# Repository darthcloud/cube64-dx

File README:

======
cube64
======

Introduction
------------

This is a project to build an adaptor for using Gamecube controllers
with N64 consoles. The motivation behind this is that the N64 has some
really great games, but the controller hardware is rather bad- the
joysticks wear out quickly, and the layout is odd. The Gamecube
controllers, however, have a superset of the features and a much
better joystick.

A secondary goal of this project is to more thoroughly reverse engineer
the protocols involved and create reusable libraries for interfacing PIC
microcontrollers to N64 and Gamecube devices. The very basics of reverse
engineering the two protocols was done before I started this project,
but I quickly discovered that there's much more to the protocol. I believe
this project may be the first one to completely reverse engineer the
protocol used by standard N64 controllers, including peripherals like the
memory and rumble paks.

All code here is released under the GPL. This means that if you have basic
electronics skills and a way to program the microcontroller, you can build
your own cube64 adaptor easily. The hardware is extremely simple, and all
the complexity of reverse engineering and writing code is done for you ;)

Usage
-----

The completed adaptor plugs into an N64 console, and a regular Gamecube
controller or Wavebird (Only for 12f683 version) plugs into the adaptor. 
The default button mapping is as follows:

   Gamecube       N64
  ---------------------
   Analog stick   Analog stick
   D-pad          D-pad
   A              A
   B              B
   Z              Z
   Start          Start
   R end-stop     R
   L end-stop     L
   C-stick        C buttons
   X              C-down
   Y              B

This button mapping is stored in non-volatile memory, and may be modified during
gameplay. To change the mapping for one button:

  1. Hold down the L and R buttons down most of the way, but not enough to
     push the end-stop buttons, and press Start.

  2. If you have the rumble power connected, you should feel a brief rumble.

  3. Press the button you wish to remap. This includes the C-stick and D-pad, since
     they emulate buttons.

  4. Press the button you want to map it to. This button is always interpreted
     according to the above defaults, so for example pressing Y here would actually
     map to B. This has the effect that pressing the same button you pressed in step
     3 always resets that button to its default mapping.

  5. If the mapping was successful and you have rumble power connected, you should feel
     a brief rumble.

To reset all mappings of the current active button layout to the above defaults:

  1. Hold down the L and R buttons down most of the way, but not enough to
     push the end-stop buttons, and press Z.

  2. If you have the rumble power connected and the reset was successful, you should
     feel a brief rumble.

To toggle between displaying the controller with empty slot and occupied slot (See notes below):

  1. Hold down the L and R buttons down most of the way, but not enough to
     push the end-stop buttons, and press X.
	 
  2. If you have the rumble power connected and the toggle was successful, you should
     feel a brief rumble.

Note 1: 
	This setting is volatile. Adapter alway start as occupied on boot.

Note 2: 
	This feature is usefull for some game that repport error with a rumble pak.
	For those games, immediately toggle to empty controller on boot to avoid the error.

It is possible to save up to 4 sets of custom buttons layouts so you can easily use different keys
mapping in different games. To change between the preset do the following (Only available in 12F683 version):

  1. Hold down the L and R buttons down most of the way, but not enough to
     push the end-stop buttons, and press one of the direction on the gamecube "cross" pad.
	 
  2. If you have the rumble power connected and the preset change was successful, you should
     feel a brief rumble.
	 
  3. All preset by default hold the default button configuration. Just select one of 4
     presets and then change the button configuration using the button mapping key combo
	 described above.

  4. When you select a preset it is saved into the eeprom so the next time you power up
     the adaptor the last used preset will be load automaticaly!

The adaptor handles calibration in almost the exact same way a Gamecube does. If
your joystick is drifting or nonresponsive during gameplay, you should be able to
recalibrate it by performing any of the following actions without touching the
joystick, C-stick, L button, or R button:

  1. Hold down X, Y, and Start for a couple seconds during gameplay

  2. Unplug the controller from the adaptor and plug it back in

  3. Unplug the adaptor from the N64 and plug it back in

  4. Turn off the N64 then turn it back on. (The reset button won't
     recalibrate, since the adaptor doesn't lose power or get reinitialized)

Hardware
--------

There are currently three versions of the Cube64 hardware:

  - The "Cube64 Basic" uses a very common PIC16F84A microcontroller, and
    requires an external 5V power supply. Just about any electronics hobbyist
    should be able to build it easily. (Deprecated)

  - The "Cube64 Mini" uses a tiny 8-pin PIC12F629 microcontroller, and
    includes a charge pump that generates the 5V supply for the rumble motor.
    It is smaller and more convenient than the Cube64 Basic, but it requires
    a less common microcontroller and a charge pump that's only available
    in surface mount packages. (Deprecated)
	
  - The "Cube64-DX" uses the PIC12F683 microcontroller. It use exacly the same
    circuit as the Cube64 Mini. It's the only version who get new feature
	since it have more flash memory to hold the additional code needed.

Both older versions of the hardware have the same button remapping features
and responsiveness, as the only difference in their firmware is a few lines
worth of compile-time configuration. You can also of course use the charge
pump circuit from the Cube64 Mini with a PIC16F84A- but if you're using
tiny chips anyway, might as well go all the way ;)

The PIC12F683 version include all new feature like multi button mapping layout,
Wavebird support and a more accurate joystick value range.

Status
------

The protocol used between the N64 and controller, and between the controller
and controller pak is well-understood now. An RS-232 to N64 bridge and several
Python programs demonstrate just about all of the protocol.

The necessary subset of the protocol has been implemented in the cube64
firmware to emulate an official N64 controller with rumble pak. If 5V power
for the motor can be supplied to the gamecube controller, its rumble motor
will be used to emulate the N64 rumble pak.

It should be possible to emulate the N64 memory pak using the results of my
reverse engineering, but a 20 MHz PIC probably isn't fast enough to run the
CRC algorithm in time to return a status byte to the N64. If a faster
implementation of the CRC is discovered or a processor about twice as fast is
used, the memory pak could be emulated easily.

Contents
--------

  firmware:  Source code for the firmware, in PIC assembly. I develop this
             mostly using the open source "gputils" package, but I occasionally
             test it with MPLAB. The firmware for the adaptor itself is
             "cube64.asm", but there are a few additional test programs
             and libraries.

  hardware:  This includes schematics for the adaptor, in PDF and gschem format.

  notes:     Utilities and documentation produced while reverse engineering

Micah Dowty <micah@navi.cx>
Jacques Gagnon <darthcloud@gmail.com>

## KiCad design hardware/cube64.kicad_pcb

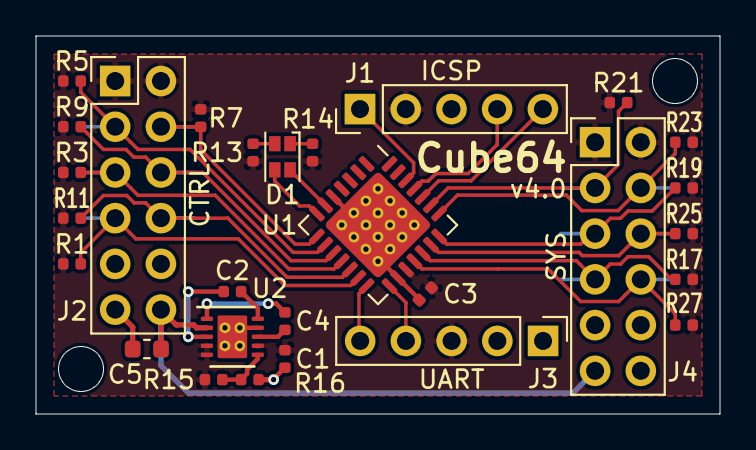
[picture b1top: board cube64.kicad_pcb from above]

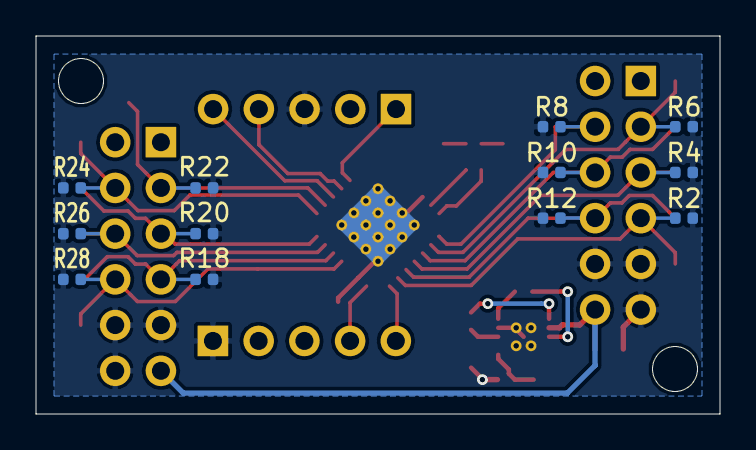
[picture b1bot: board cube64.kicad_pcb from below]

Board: 2 copper layers, 38.0 x 21.0 mm, 40 parts (12 on the bottom side), 29 nets.

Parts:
C1, C2, C4: 2.2u; C_0402_1005Metric
C3: 0.1u; C_0402_1005Metric
C5: 4.7u; C_0603_1608Metric
D1: LED_Dual_AACC; D_0606_1616Metric
J1: ICSP; PinHeader_1x05_P2.54mm_Vertical
J2: CTRL; PinHeader_2x06_P2.54mm_Vertical
J3: UART; PinHeader_1x05_P2.54mm_Vertical
J4: SYS; PinHeader_2x06_P2.54mm_Vertical
R1, R2, R4, R5, R6, R7, R8, R10, R11, R12, R17, R18, R19, R20, R21, R22, R23, R24, R25, R26, R27, R28: DNP; R_0402_1005Metric
R3, R9: 1K; R_0402_1005Metric
R13, R14: 64.9; R_0402_1005Metric
R15: 402K; R_0402_1005Metric
R16: 100K; R_0402_1005Metric
U1: PIC18F24Q10; QFN-28-1EP_6x6mm_P0.65mm_EP4.25x4.25mm_ThermalVias
U2: LTC3203B-1; DFN-10-1EP_3x3mm_P0.5mm_EP1.55x2.48mm

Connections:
+3V3: C1.1, C3.1, J1.2, J2.1, J2.2, J3.3, J4.1, J4.2, R1.1, R3.1, R5.1, R7.1, R9.1, R11.1, R13.1, R14.1, R15.1, R17.1, R19.1, R21.1, R23.1, R25.1, R27.1, U1.17, U2.4, U2.5, U2.7
+5V: C5.1, J2.12, J4.11, U2.2
/CTRL0: J2.4, R7.2, R8.1, U1.8
/CTRL1: J2.3, R5.2, R6.1, U1.9
/CTRL2: J2.6, R9.2, R10.1, U1.10
/CTRL3: J2.5, R3.2, R4.1, U1.11
/CTRL4: J2.8, R11.2, R12.1, U1.12
/CTRL5: J2.7, R1.2, R2.1, U1.13
/G_LED: D1.3, U1.6
/PGC: J1.5, U1.24
/PGD: J1.4, U1.25
/R_LED: D1.4, U1.7
/SYS0: J4.3, R21.2, R22.1, U1.23
/SYS1: J4.4, R23.2, R24.1, U1.22
/SYS2: J4.5, R19.2, R20.1, U1.21
/SYS3: J4.6, R25.2, R26.1, U1.20
/SYS4: J4.7, R17.2, R18.1, U1.19
/SYS5: J4.8, R27.2, R28.1, U1.18
/UART_RX: J3.4, U1.15
/UART_TX: J3.5, U1.14
GND: C1.2, C3.2, C5.2, J1.3, J2.9, J2.10, J2.11, J3.1, J4.9, J4.10, J4.12, R2.2, R4.2, R6.2, R8.2, R10.2, R12.2, R16.2, R18.2, R20.2, R22.2, R24.2, R26.2, R28.2, U1.5, U1.16, U1.29, U2.9, U2.11
unnamed: C2.1, U2.3
unnamed: C2.2, U2.10
unnamed: C4.1, U2.1
unnamed: C4.2, U2.8
unnamed: D1.1, R14.2
unnamed: D1.2, R13.2
unnamed: R15.2, R16.1, U2.6
VPP: J1.1, U1.26

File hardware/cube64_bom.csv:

Component,Description,Part,References,Value,Footprint,Quantity Per PCB,Datasheet,Digikey Part
1,Unpolarized capacitor,C,C3,0.1u,C_0402_1005Metric,1,~,1276-1004-1-ND
2,Unpolarized capacitor,C,C1 C2 C4,2.2u,C_0402_1005Metric,3,~,1276-1888-1-ND
3,Unpolarized capacitor,C,C5,4.7u,C_0603_1608Metric,1,~,1276-1907-1-ND
4,"LED dual, 4-pin",LED_Dual_AACC,D1,LTST-C195KGJRKT,D_0606_1616Metric,1,https://media.digikey.com/pdf/Data%20Sheets/Lite-On%20PDFs/L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,160-1452-1-ND
5,Resistor US symbol,R,R16,100K,R_0402_1005Metric,1,~,RMCF0402JT100KCT-ND
6,Resistor US symbol,R,R3 R9,1K,R_0402_1005Metric,2,~,311-1.0KJRCT-ND
7,Resistor US symbol,R,R15,402K,R_0402_1005Metric,1,~,YAG3151CT-ND
8,Resistor US symbol,R,R13 R14,64.9,R_0402_1005Metric,2,~,RMCF0402FT64R9CT-ND
9,,LTC3203B-1,U2,LTC3203B-1,DFN-10-1EP_3x3mm_P0.5mm_EP1.55x2.48mm,1,http://www.linear.com/docs/15197,LTC3203BEDD-1#PBF-ND
10,,PIC18F24Q10,U1,PIC18F24Q10,QFN-28-1EP_6x6mm_P0.65mm_EP4.25x4.25mm_ThermalVias,1,http://www.microchip.com/mymicrochip/filehandler.aspx?ddocna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,PIC18F24Q10-I/ML-ND





Component Groups:,13
Component Count:,40
Fitted Components:,14
Number of PCBs:,1
Total components:,14
Schematic Version:,A
Schematic Date:,2018-10-10
BoM Date:,Wed 10 Oct 2018 10:24:46 PM EDT
Schematic Source:,cube64-dx/hardware/cube64.sch
KiCad Version:,Eeschema 5.0.0-fee4fd1~66~ubuntu18.04.1

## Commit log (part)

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2004-08-06 Move cube64 into wasabi/devices, it seems to be the trendy place to be these days
2004-08-06 Sprinkle this with #ifdef'ed no-ops that might magically make this work at 24 MHz too
2004-08-07 Some N64/gamecube timing fixes for 24Mhz. This is still untested, but it works in my head...
2011-03-26 cube64.asm: -Added support for identify command 0xFF. (Fixed issue #2) -Added support for 12F683 micro.
    Makefile:
    -Added support for 12F683 micro.
    n64gc_comm.inc:
    -Added support for identify command 0xFF. (Fixed issue #2)
    -Fixed typo about n64/ngc serial format.
2011-03-28 cube64.asm: -Added possibility to toggle between controller status id. Either occupied or empty with AL+AR+X key combo. (Enhancement #4 done)
2011-03-29 cube64.asm: -Added support for Wavebird (Enhancement #5 done) -Skip rumble update when in mode "slot empty"
2011-03-29 cube64.asm: -Minor typo in CRC table address for smaller PIC.
2011-03-31 cube64.asm: -Removed very ugly code repetition in the multi key layout selection section.
2011-04-02 cube64.asm: -GameCube axis range ~[24, 232] now correctly translated into N64 axis range ~[-84, 84]. (Fixed issue #7)
2011-04-02 Created wiki page explaining how to compile from source.
2011-04-03 Created wiki page to show how to program the PIC
2011-04-03 Edited wiki page WikiProgrammingThePIC through web user interface.
2011-04-03 Typo fixing.
2011-04-03 Edited wiki page Readme through web user interface.
2011-04-04 cube64.asm: -Unlike what is write in many source for both N64 and Gamecube, the controller response always end with a 2us stop bit. In Micah docs he say this is only done for CRC response. But from w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
    So I removed the n64_tx_widestop and modified n64_tx to always used 2us stop bit.
2011-04-04 Deleting wiki page WikiCompilingFromSource.
2011-04-04 Deleting wiki page WikiProgrammingThePIC.
2011-04-13 cube64.asm: -Their where not any n64_status_buffer initialization when a Wavebird receiver is not associated with a WB. Added n64_status_buffer initialization at the beginning. (Fixed issue #8)
2011-04-13 cube64.asm: -Better fix of n64_status_buffer bug with Wavebird, always clear buffer before calling n64_wait_for_command. -When a Wavebird is connected to the adapter, Cube64-DX now report to the n64 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
2011-04-13 cube64.asm: -Little code cleanup.
2011-04-14 cube64.asm: -Now EEPROM reset combo only affect the current active button mapping layout.
2011-04-15 Added schematic for PIC12F683
2011-04-17 cube64.asm: -Fixed a bug with 16F84A EEPROM introduced by multi layout feature in 12F683 version.
2011-04-17 Edited wiki page BuildingAdapter through web user interface.
2011-04-17 Some change to reflect current adapter status.
2011-04-20 Removed support for older microcontroller.
    cube64.asm:
    -Added a deadzone to the GC joystick to fix some issue with Wavebird.
2011-04-22 cube64.asm: -Some little cleanup in variable declaration.
2011-04-28 Edited wiki page FlashingFirmware through web user interface.
2011-05-08 cube64.asm: -Implemented new key combo handling method. All option are accessed now via a config menu (Accessed by pressing AL+AR+Start). Once in the menu you can enter remap function by pressing Sta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
    Their is two submenu currently. The adapter mode submenu is accessed by pressing D-pad UP while the button layout submenu is accessed by pressing D-pad LEFT.
    In adapter mode submenu pressing UP make the adapter show as controller with empty slot while pressing LEFT make it show as controller with Rumble Pak.
    In layout selection submenu, each D-pad direction select one of the 4 button mapping layout.
2011-05-08 cube64.asm: -Now possible to select on boot the adapter mode by pressing the D-pad direction. Option layout is the same as the layout selection submenu.
2011-08-13 cube64.asm: -Redone some CR removed with last commit.
2011-11-03 Added new folder (firmware64) for upcoming implementation running at 64MHz.
2011-12-06 New firmware version running on PIC18F14K22 @ 64MHz.
2018-01-04 Make EEPROM mapping more versatile
    Will allow additional axes & buttons to be remapped.
2018-01-04 Add .gitignore
    Ignore hex, cod, lst & pyc files
2018-01-04 Use TMR0 for rumble feedback time base
    Using system polling rate could often result in rumble to be too short to be felt.
    This provides a consistent 250 ms rumble feedback.
2018-01-04 Get ride of the TABs
    This break blame but it's a good tradeoff IMHO :)
2018-01-04 Add second config byte in EEPROM for each virtual buttons
    Required for future features.
2018-01-04 Split out definitions in cube64.inc file
2018-01-04 Cleanup configuration menu implementation
    Cosmetic only, no behavior change.
2018-01-04 Turn modifier bit into special function bit
    Will be used for additional internal functions.
2018-01-04 Make virtual buttons definitions more future proof
    That should allow changing the front end to any modern controllers.
2018-01-04 Add realtime CRC computation base on the large table
    This fix Banjo-Kazooie & GoldenEye 007 Rumble Pak mode (Issue #1)
2018-01-04 Specify python2 in scripts header
2018-01-04 Update documentation for v3.0 release
2018-01-04 New firmware version running on PIC18F14K22 @ 64 MHz
    Port Cube64 from PIC12F683 @ 20 MHz to PIC18F14K22 @ 64 MHz.
    The speed increase will allow computing the CRC.
2018-01-04 Revert "Firmware64"
2018-01-04 Add function to modify mapping layout with a button press
    Pressing the Y button at the top level menu will allow
    mapping a special function to the source button.
    The destination consists of one of the 4 D-pad directions who
    correspond respectively to one of the mapping layouts.
    While holding a button set to this function, the current
    mapping layout configured will be overwritten until
2018-01-04 N64 bus read now receive the 2 address bytes
    If the address is 0x8001 we answer with a packet of 0x80s.
    Otherwise send 0x00s.
    This make us answer a bit slower (~14 μs) than before (~10 μs) but
    the N64 gonna wait for us up to 80 μs base on my tests.
2018-01-04 Default serial bridge to normal polarity and script to /dev/ttyUSB0
    For use with FTDI TL-232R-3V3 cable.
2018-01-04 Allow selecting either digital or analog triggers for mapping
    By default button remap and special function combos will map to
    digital trigger buttons only.
    Pressing X in the main menu before either Start or Y will enable
    mapping to the analog trigger axes.
2018-01-04 Script for polling N64/GC SI bus devices
    This script uses the serial bridge and pool in loops
    for the buttons status.
    It currently supports N64 controllers, N64 mouses & GameCube controllers.
2018-01-05 Clear FLAG_TRIGGER when special function map abort
    The trigger flag would remain set if an invalid option was
    chosen in the special function mapping.
2018-02-06 Update documentation for v3.1 release
2018-02-06 Port Python 2 scripts to Python 3
    Use pySerial for serial bridge communication.
    Convert string usage to bytes.
    Fix prints and sorts.
2018-02-06 Add bypass mode for using N64 controller as accessory slot
    Fixes #10
    The adaptor can now have a N64 controller attach to it on RA2 to be
    used as an accessory slot. Once in this mode the adaptor will only
    answer the button status commands. All other commands will be copied to
    the N64 controller. Then the controller response is copied back to the
    system.
2018-05-22 Make adaptor mode non-volatile
    Quick hack to save the last used mode in EEPROM.
    Not in the main branch as I don't really like it myself. :)
    But some might prefer this.
2018-06-01 Add access bits
2018-06-01 Update documentation for v3.2 release
2018-06-01 Switch to banked access
    Will need to use the access mode for literal offset addressing later.
2018-06-01 Split joystick scaling on/off switch on two buttons
    Easier to tell if it's on or off.
2018-06-01 Align in-line comments
2018-06-06 Support 1 player 2 controllers control style
    GoldenEye and Perfect Dark got a control style using
    two controllers as a way to get dual analog sticks.
    Since the adaptor is now interrupt base it's quite easy now
    to answer another poll on another pin.
    This duplicate the mapping of the C buttons (as analog) and R buttons into
    second set of buffers for the second controller.
2018-06-21 Move 2nd controller pin to PORTB6
    Let's not overlap with the UART RX pin.
2018-06-21 Update documentation for v3.3 release
2018-06-21 Add LED to indicate we are in the menu
2018-06-21 Answer N64 poll within WaveBird init
2018-06-21 Add response curves option for each GC joystick axes
    This feature adds a new menu option DPAD-RIGHT in the top menu. Once in
    that submenu you can select one of the four joysticks axes of the GC
    controller by pressing either direction of one of those axes. Finally at
    the last level of the submenu you can select the following options:
    D-PAD UP: Map selected joystick axis through an aggressive response curve.
    D-PAD LEFT: Map selected joystick axis through a relaxed response curve.
2018-06-21 Mute joysticks input while in menu
2018-07-07 Restore RA4 transition detection in serial bridge
    Somehow the published version from 2004 do not check for
    transition on RA4, it rather sent TMR0 value.
    Fix up as well couple Python 3 script issue.
    It's purely academic but it allows recreating Micah original
    experiment from 2004!
    Traces done with the serial bridge on the controller bus are
2018-10-06 Pre-defined mapping layout presets
    Add a new entry in the main menu via D-pad DOWN for pre-defined mapping layout presets.
    Eight preset are available on flash to be copied in one of the four mapping banks in the EEPROM.
    After pressing D-pad DOWN in the menu, the next input on the 4 D-pad or 4 main joystick direction
    will load the presets chosen in the currently active mapping layout bank in the EEPROM.
    See wiki for presets detail.
2018-10-06 Cleanup IOs & fixup bank bits
    Enable weak pull up on all 4 SI pin.
    Set unused pin to output low.
    No longer need to check if the 2nd controller port is plugin at
    boot to enable interrupt. The weak pull up will prevent
    triggering the interrupt.
    Remove PORTC debug.
2018-10-06 EEPROM init hardening
    Observed some glitch in EEPROM init sometimes.
    Move interrupt handling out of the EEPROM reset function.
    Revalidate EEPROM after init.
    Also fixup unneeded double init of the first layout bank.
2018-10-06 Add a special two-button mapping for A+C-Down & B+C-Left
    In all three Tony Hawk's games the only right side face buttons used are
    the C Buttons, while in the menu only the A & B buttons are used.
    Mapping the GC face buttons to C Buttons make menu navigation
    annoying.
    Since there is no overlap between the menu and gameplay, this
    special mapping function merge on the same buttons both the A & C-Down
2018-10-06 Turbo buttons feature
    Using special function menu any GC button or axis can be set to one of
    3 turbo speed:
    C-Up: No turbo
    C-Left: Faster turbo: 1 frame set, 1 frame clear.
    C-Right: Medium turbo: 2 frame set, 2 frame clear.
    C-Down: Slower turbo: 2 frame set, 14 frame clear.
2018-10-17 Add support for Q10 and PICKIT4 in Makefile
2018-10-17 Ignore KiCad backup and IPECMD logs
2018-10-17 Update documentation for v4.0 release
2018-10-17 Add Q10 support for adaptor
2018-10-17 KiCad PCB design for Q10 mcu
2018-10-17 Add dual LED support for Q10
    LED will be Green in menu level 1, Orange in level 2 and Red in level 3.
2018-11-19 Allow in GoldenEye to shoot/switch weapon in the cut-scene via 2nd CTRL
    This is a speed run trick that requires two changes in the
    1 player 2 controllers feature:
    1. A new special button that can be mapped via X in the special
    feature menu. When pressed, this special button will mute the
    buttons reported to the first controller slot (Exept Z & Start).
    Without the mute the press on the 1st controller would skip the cut scene.
